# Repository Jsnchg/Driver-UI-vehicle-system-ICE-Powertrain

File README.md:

# Driver-UI-vehicle-system-ICE-Powertrain

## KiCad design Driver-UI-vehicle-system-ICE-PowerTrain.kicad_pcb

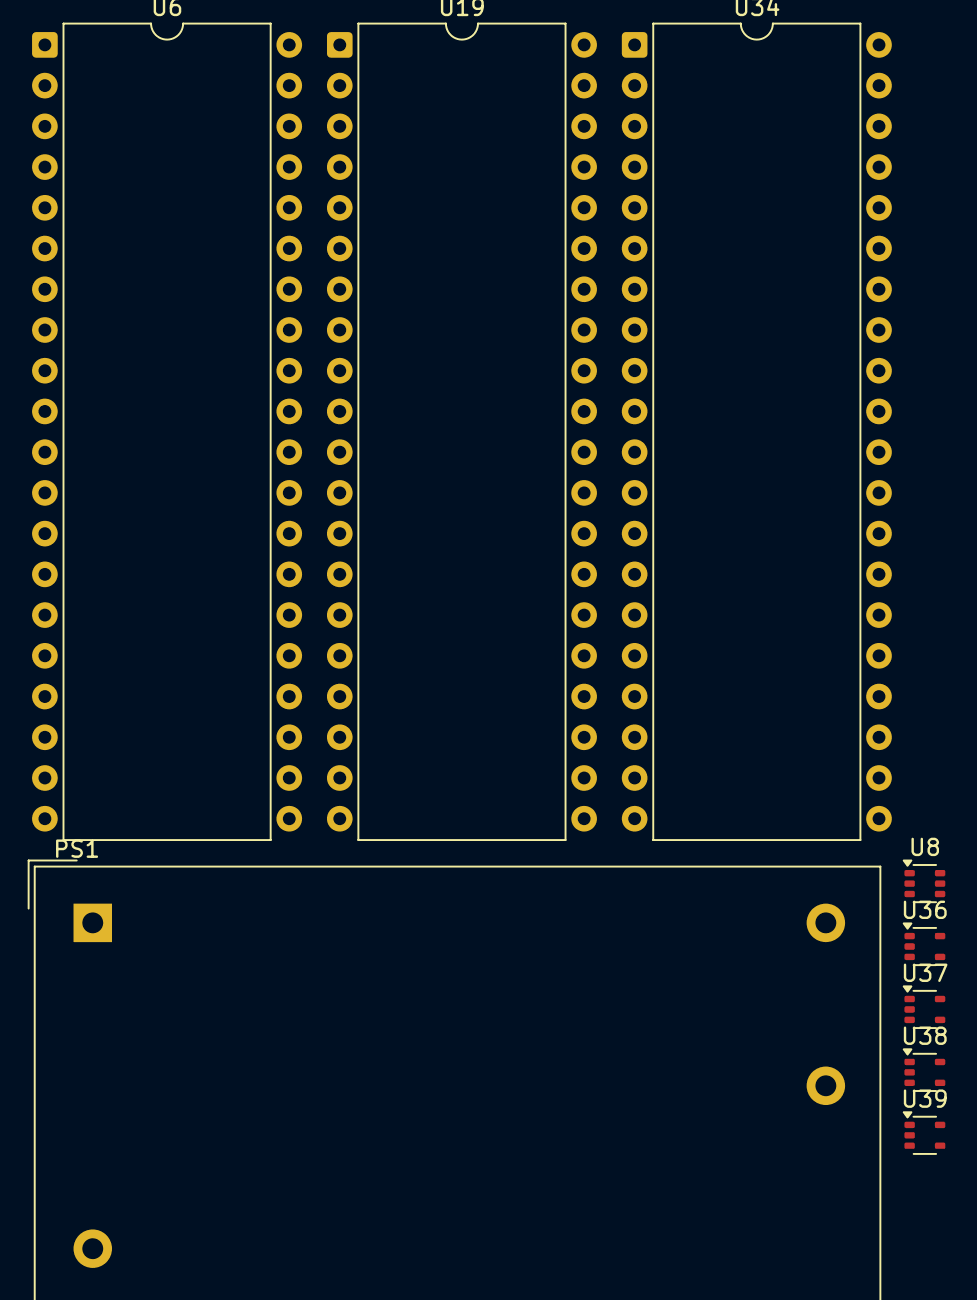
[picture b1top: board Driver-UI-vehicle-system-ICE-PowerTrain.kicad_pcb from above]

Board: 2 copper layers, 9 parts (0 on the bottom side), 10 nets, no tracks yet.

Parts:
PS1: RAC20-05SK; Converter_ACDC_Recom_RAC20-xxSK_THT
U6, U19, U34: 8080; DIP-40_W15.24mm
U8: NCS210; SOT-363_SC-70-6
U36, U37, U38, U39: TLV172IDCK; SOT-353_SC-70-5

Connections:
GND: PS1.1 (AC(N)), PS1.4 (-Vout)
unnamed: PS1.5 (+Vout), U38.1 (+), U38.3 (-)
unnamed: U19.20 (+5V), U19.28 (+12V)
unnamed: U6.25 (A0), U8.3 (Vs)
unnamed: U6.26 (A1), U8.4 (+IN)
unnamed: U6.27 (A2), U8.5 (-IN)
unnamed: U34.25 (A0), U36.1 (+)
unnamed: U34.26 (A1), U36.3 (-)
unnamed: U34.27 (A2), U37.1 (+)
unnamed: U34.29 (A3), U37.3 (-)
